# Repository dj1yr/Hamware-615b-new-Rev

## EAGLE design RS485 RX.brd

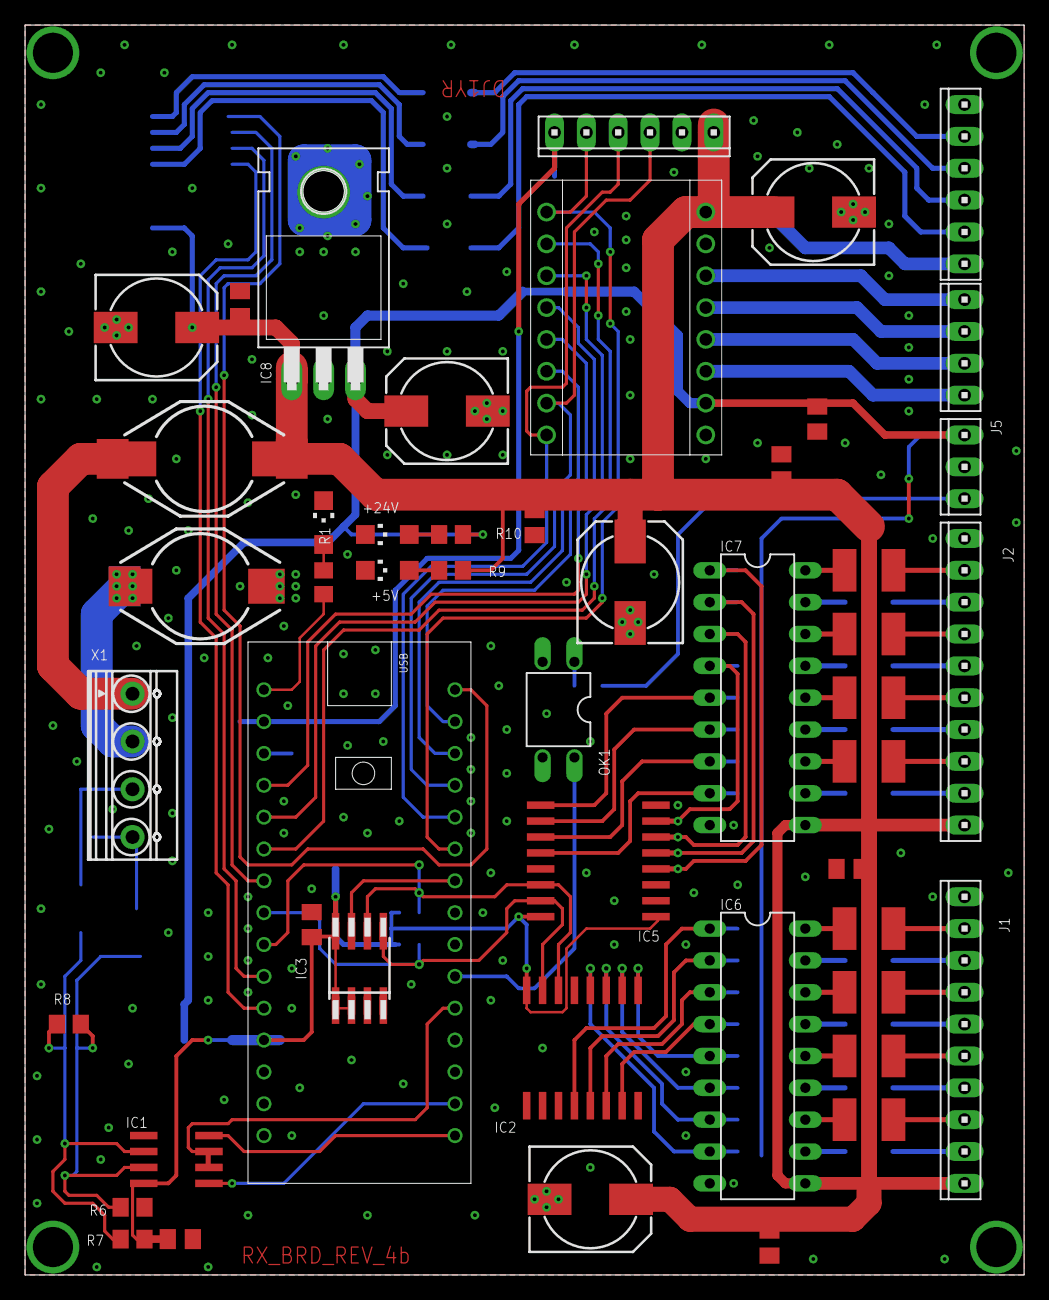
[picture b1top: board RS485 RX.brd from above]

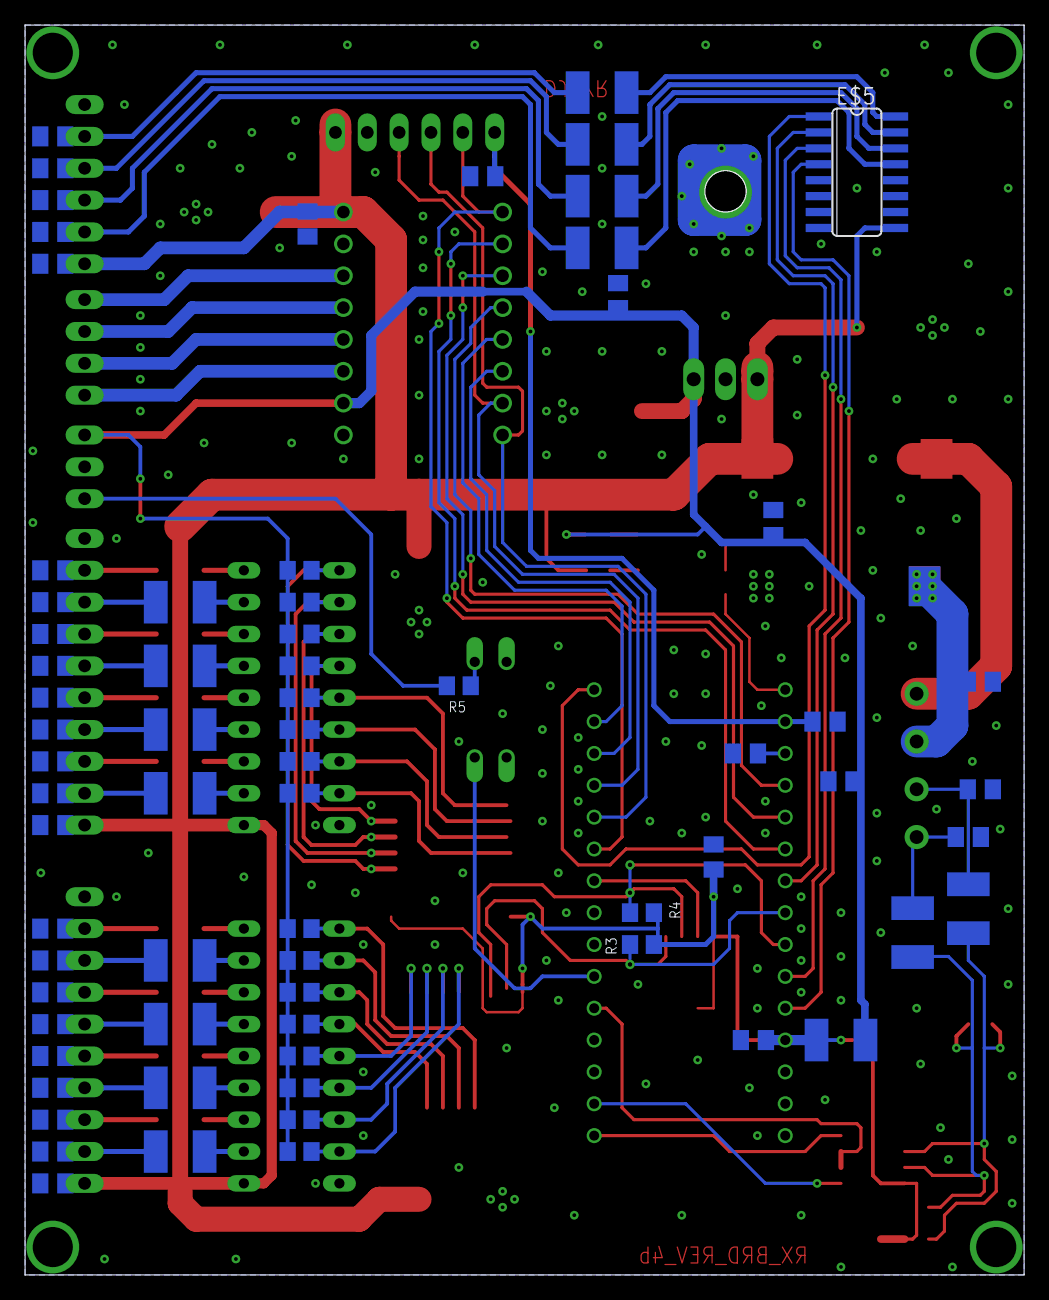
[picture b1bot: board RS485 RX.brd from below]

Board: 2 copper layers, 79.7 x 99.7 mm, 118 parts (70 on the bottom side), 62 nets.

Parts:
+5V, +5V1, +24V: CHIPLED_1206
C1, C6, C7, C8, C9, C10, C11, C12, C13, C14, C15, C16, C17, C18, C19, C20, C21, C22, C23, C24, C25, C26, C27, C28, C29, C30, C31, C32, C33, C34, C35, C36, C37, C38, C39, C40, C42, C43, C44, C45, C46, C47, C48: C0805K
C2, C3, C5: 10µ; 150CLZ-0810
C4, C41: 100µ; 150CLZ-0810
E$1: 10X04MTA
E$2, E$3: DO3316P
E$4: SO-08M
E$5: SO16
E$7: 10X06MTA
IC1: LTC485S; SOIC8
IC2, IC5: PCF8574T; SO16W
IC3: 24LC128SN; SO-08
IC6, IC7: DIL18
IC8: 78S05T; TO220H
J1, J2: 10X10MTA
J3: 10X06MTA
J5: 10X03MTA
L1, L2, L3, L4, L5, L6, L7, L8, L9, L10, L11, L12, L13, L14, L15, L16, L17, L18, L19, L20, L21, L22, L23: L1812
OK1: PC817; DIL04
R1, R9: 3k3; R0805
R3, R4, R6, R7: 4k7; R0805
R5, R10: 330R; R0805
R8: 120R; R0805
R11, R12, R13, R14, R15, R16, R17, R18, R19, R20, R21, R22, R23, R24, R25, R26: 10k; R0805
X1: 1727036

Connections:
3V3: C47.1, C48.1, E$7.1
+5V: IC1.8, IC2.16, IC3.8, IC5.16, J5.1, L1.2, R3.2, R4.2, R7.2, R10.2
+24V: C41.+, E$7.6, IC6.10, IC7.10, IC8.1, J1.10, J2.10, J3.6, R9.1
GND: +5V.C, +5V1.C, +24V.C, C1.2, C2.-, C3.-, C4.-, C5.-, C6.2, C7.2, C8.2, C9.2, C10.2, C11.2, C12.2, C13.2, C14.2, C15.2, C16.2, C17.2, C18.2, C19.2, C20.2, C21.2, C22.2, C23.2, C24.2, C25.2, C26.2, C27.2, C28.2, C29.2, C30.2, C31.2, C32.2, C33.2, C34.2, C35.2, C36.2, C37.1, C38.1, C39.1, C40.1, C41.-, C42.2, C43.2, C44.2, C45.2, C46.2, C47.2, C48.2, E$3.2, E$5.8, E$7.5, IC1.5, IC2.1, IC2.2, IC2.3, IC2.8, IC3.3, IC3.4, IC5.2, IC5.3, IC5.8, IC6.9, IC7.9, IC8.2, J1.1, J2.1, J3.1, J5.2, OK1.2, OK1.3, R6.2
unnamed: IC2.4, IC6.1
unnamed: IC2.5, IC6.2
unnamed: IC2.6, IC6.3
unnamed: IC2.7, IC6.4
unnamed: IC5.4, IC7.1
unnamed: IC5.5, IC7.2
unnamed: IC5.6, IC7.3
unnamed: IC5.7, IC7.4
unnamed: IC5.9, IC7.5
unnamed: IC5.10, IC7.6
unnamed: IC5.11, IC7.7
unnamed: IC5.12, IC7.8
unnamed: IC6.18, L2.1
unnamed: IC6.17, L3.1
unnamed: IC6.16, L4.1
unnamed: IC6.15, L5.1
unnamed: IC6.14, L6.1
unnamed: IC6.13, L7.1
unnamed: IC6.12, L8.1
unnamed: IC6.11, L9.1
unnamed: IC7.18, L10.1
unnamed: IC7.17, L11.1
unnamed: IC7.16, L12.1
unnamed: IC7.15, L13.1
unnamed: IC7.14, L14.1
unnamed: IC7.13, L15.1
unnamed: IC7.12, L16.1
unnamed: IC7.11, L17.1
unnamed: J1.2, L2.2
unnamed: J1.3, L3.2
unnamed: J1.4, L4.2
unnamed: J1.5, L5.2
unnamed: J1.6, L6.2
unnamed: J1.7, L7.2
unnamed: J1.8, L8.2
unnamed: J1.9, L9.2
unnamed: J2.2, L10.2
unnamed: J2.3, L11.2
unnamed: J2.5, L13.2
unnamed: J2.6, L14.2
unnamed: J2.7, L15.2
unnamed: J2.8, L16.2
unnamed: J2.9, L17.2
unnamed: J2.4, L12.2
unnamed: OK1.1, R5.1
unnamed: IC2.12, IC6.8
unnamed: IC2.11, IC6.7
unnamed: IC2.10, IC6.6
unnamed: IC2.9, IC6.5
unnamed: J5.3, R5.2
unnamed: L18.2, R6.1, R8.1
unnamed: L19.2, R7.1, R8.2
unnamed: C1.1, L1.1
unnamed: +5V.A, R9.2
unnamed: +24V.A, R10.1
RS_EN: IC1.2, IC1.3
SCL: IC2.14, IC3.6, R4.1
SDA: IC2.15, IC3.5, IC5.15, R3.1

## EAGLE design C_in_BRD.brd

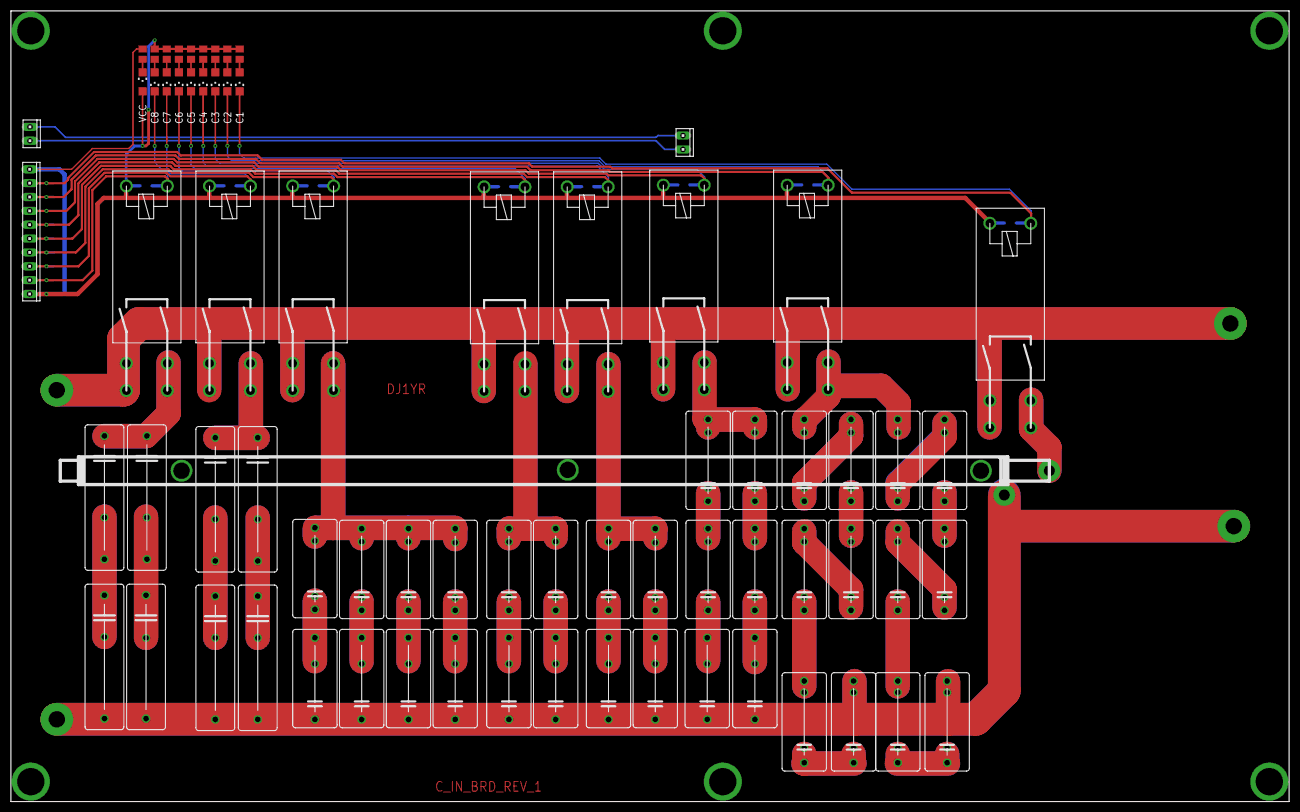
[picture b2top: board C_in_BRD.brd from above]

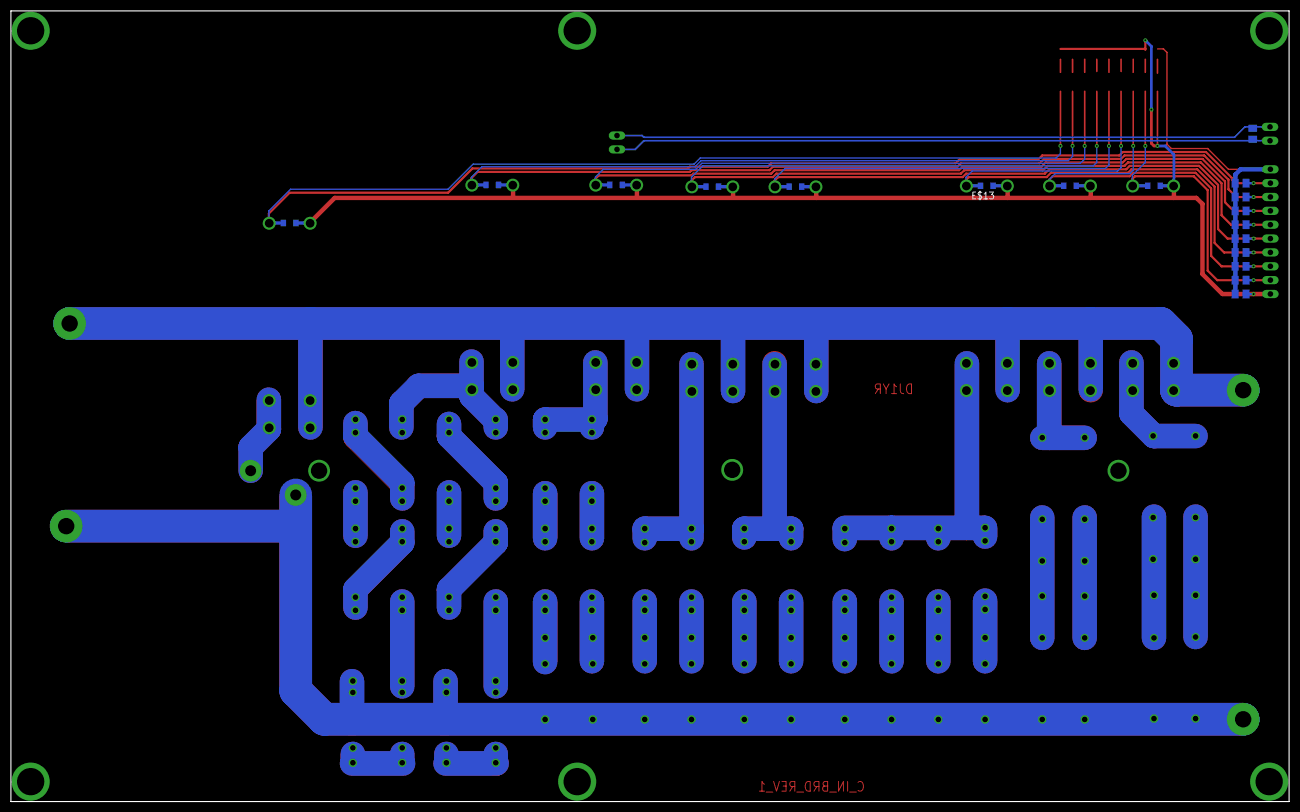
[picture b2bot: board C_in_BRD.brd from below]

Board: 2 copper layers, 234.3 x 144.9 mm, 89 parts (18 on the bottom side), 2 nets.

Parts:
C1, C2, C3, C4, C5, C6, C7, C8: CHIPLED_1206
C_1, C_2, C_3, C_4: 2200/2KV; C225-074X268
C_5, C_6, C_7, C_8: 1000/2KV; C225-074X268
C_9, C_10, C_11, C_12, C_17, C_18, C_19, C_20: 330/2KV; C150-084X183
C_13, C_14, C_15, C_16: 220/2KV; C150-084X183
C_21, C_22, C_23, C_24: 150/2KV; C150-084X183
C_25, C_26, C_27, C_28, C_29, C_30, C_31, C_32, C_33, C_34, C_35, C_36, C_37, C_38, C_39, C_40, C_41, C_42: 100/2KV; C150-084X183
E$1: 10X10MTA
E$2, E$3, E$4, E$5, E$6, E$7, E$8, E$9, E$10, E$20: C0805K
E$11, E$12, E$13, E$14, E$15, E$16, E$17, E$18: SOD110-W
E$19, E$21: 10X02MTA
E$22, E$23, E$24, E$25, E$26, E$27, E$28, E$29, E$30: R0805
U$1, U$2, U$3, U$4, U$5, U$6, U$7, U$8: FINDER45.91.7.024.0310
VCC: CHIPLED_1206

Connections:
S$24: E$2.2, E$3.2, E$4.2, E$5.2, E$6.2, E$7.2, E$8.2, E$9.2, E$10.2
S$97: E$19.2, E$21.2
